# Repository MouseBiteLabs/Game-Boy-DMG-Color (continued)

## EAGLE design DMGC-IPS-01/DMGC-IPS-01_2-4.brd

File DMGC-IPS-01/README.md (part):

# DMGC-IPS-01

*The image above of the assembled board is of v2.0, not the current revision of v2.4. The differences are very minor, see below.*

The IPS board is in the front of the DMG shell. This holds the IPS screen kit (and has pads for interfacing with it), has the dimmable power LED, button inputs along with pads for optional LEDs, a navigation switch on the side for changing settings on the IPS screen and the backlit buttons, and the speaker.

For a technical explanation of the CPU board, please view the README in the Technical folder.

## Board Characteristics

The zipped folder contains all the gerber files for this board.
-	Layers: 2
-	Thickness: 1.2 mm
-	Surface Finish: ENIG or HASL (SEE NOTE!)

*ENIG is required for reliable button press detection; you can use HASL if you are using tactile switches.*

<a href="https://www.etsy.com/listing/1331663235/game-boy-dmgc-ips-board">**I sell this board on Etsy, so you don't have to buy multiples from board fabricators.**</a>

You can alternatively use the zipped folder at any board fabricator you like. You may also buy the board from PCBWay using this link (disclosure: I receive 10% of the  sale value to go towards future PCB orders):

## Customization Options

This section will explain all of the different customization options available on this board while assembling.

### Tactile Switches

Version 2.0 introduced the option for including tactile switches for the buttons, much like the Game Boy Advance SP had. If you do not wish to use these kinds of buttons, the button contacts are still set up to act just like the regular set up with membranes.

In this image, tactile switches are on the left, and pads for simple membranes are on the right. Either method for button presses works perfectly fine. But make sure you put them in the correct way. The little "wings" on the switches should be oriented where there is blank board space.

If you're doing tactile switches on the start and select buttons, you should do a trace cut as indicated where the white lines are pointing. If you don't, the membranes can still activate the start/select buttons on the exposed area without actuating the tactile switch. You may also want to tape over the exposed copper not underneath the switches while soldering them on to avoid getting stray solder on the exposed traces and ruin the A E S T H E T I C.

### Power LED Brightness

Increase the value of R1 to decrease the brightness of the power LED during normal battery levels. Increase the value of R2 to decrease the brightness of the power LED during low battery levels. It is suggested to try changing resistances in ~5 kΩ increments.

### Backlit Buttons

There are a few different avenues to take with respect to the button LEDs. You can use the RGB NeoPixels, discrete always-on LEDs, or none at all.

1) **No Button LEDs:** You do not need to populate LED10-LED17, R9, R22-R29, C2, or U2. Carry on.

2) **Always-on Single Color Backlit Buttons:** If you only want backlit buttons with non-controllable LEDs, you can omit R9, C2, and U2. 

You must isntead install R22-R29, as well as the discrete 0603 LEDs. An 0603 LED will fit on half of the 4-pin RGB LED pads, from VDD to DO. The pads for this are indicated by the arrows. The picture below shows which pads to use for discrete LEDs (view of the D-pad) - the A indicates the anode of the diode. There are spaces for a resistor for each LED on the back of the board (R22 to R29, circled in red below). If you're using the RGB LEDs, or no LEDs at all, the resistors aren't necessary. R22-R29 control the brightness of the LEDs, so keep in mind a higher resistance means lower brightness.

3) **RGB Backlit Buttons:** If you would like RGB LEDs behind the buttons, you must install LED10-LED17, R9, C2, and U2. Do not populate R22-R29.

When you solder the LEDs on, I recommend taping off the button contacts to make sure you don't get solder on them. It won't damage them to the point of non-function, but it can potentially reduce their useful lifetime and accurate detection depending on the severity. (But more importantly, it's not A E S T H E T I C)

If you install the LEDs and determine they just aren't for you, but don't want want to spend time removing the LEDs themsleves, then bridging the solder pad labeled "NEOPIXEL DISABLE" will ground the navigation switch push function, preventing the LEDs from turning on at all.

#### Programming the ATTINY85

An easy way to program the ATTINY with the code for the backlit buttons is to use an Arduino Uno or Arduino Mega. Check out these tutorials for how to program ATTINY chips with them:

-	<a href="https://www.instructables.com/How-to-Burn-ATTiny85-Using-Arduino-Mega/">Instructables post for programming an ATTINY85 with an Arduino Mega</a>
-	<a href="https://www.instructables.com/How-to-Program-an-Attiny85-From-an-Arduino-Uno/">Instructables post for programming an ATTINY85 with an Arduino Uno</a>

The code is provided above (the .ino file) and you will likely need to install Adafruit's NeoPixel library as well to get it to compile correctly. That can be found here:

- <a href="https://learn.adafruit.com/adafruit-neopixel-uberguide/arduino-library-installation">Installing Adafruit's NeoPixel Library to Arduino IDE</a>

If you're programming the ATTINY while it's installed on the IPS board, be sure to remove the cables from J1 and J2, otherwise your Arduino will attempt to backfeed the Gameboy and/or the IPS screen kit.

You can use the 7-pin connector on the side of the IPS board to connect to the ATTINY if it's already on the PCB. (You don't need the 3.3V pin to program, it's there for helping you develop your own ATTINY code if you want to use it)

**NOTE: VERSION DIFFERENCE**

On the v2.0 and v2.1 boards, pins 1 and 8 are flipped! And the 3.3V pin does not exist.

### Adding Reset Button Functionality

- If you are using the push function of the navigation switch to reset the console instead of controlling the button LEDs (see more info on the CPU README), then **make sure to remove R10.** You will not have the ability to control Neopixel LEDs with this change (without other code/hardware modifications).
- If you are using the rock down function of the navigation switch to reset the console instead of controlling the Q5 palette setting (see more info on the CPU README), then **make sure to remove C5.** You will not have the ability to use the palette swap function of the Q5 kit with this change (but who really cares, amirite?)

### Alternate OSD Controls

You don't need to use the SEL, A, and B pads at the top of the board for the OSD controls. You can alternatively use the button pads in the middle of the board instead. For example, if you intend to use LSDJ on the DMGC, you might run into a conflict with pressing A + B + Select. This is a specific combination for control in LSDJ. So instead for OSD control, you can run wires down to the middle of the board. Instead of A, B, and Select, you could pick A, B, and Start for example. Just keep in mind you have to press all three at the same time to open the menu, so don't pick Left and Right as two of the inputs, for example.

## Bill of Materials

Here, I have provided links to components I used personally (or suitable replacements). This BOM is also included in Excel format in the root folder.

| Reference Designators   | Qty | Value/Part Number | Package             | Description                       | Comment                                                                                                                            | Source                                                                                                                                                                                                                               |
| ----------------------- | --- | ----------------- | ------------------- | --------------------------------- | ---------------------------------------------------------------------------------------------------------------------------------- | ------------------------------------------------------------------------------------------------------------------------------------------------------------------------------------------------------------------------------------ |
| B1-B8                   | 8   | SKRRABE010        |                     | Tactile switch                    | Optional, can be omitted if you don't want clicky SP-style buttons (SKRRAA is less clicky, SKRRAC is more clicky)                  | [https://www.mouser.com/ProductDetail/688-SKRRAB](https://www.mouser.com/ProductDetail/688-SKRRAB)                                                                                                                                   |
| C1, C2, C6, C7, C8, C24 | 6   | 0.1uF             | 0603                | Capacitor (MLCC)                  | Should be X5R (or better), at least 16V                                                                                            | [https://www.mouser.com/ProductDetail/?qs=l5k%252BbMnNDknCtKnMv1oEgA%3D%3D](https://www.mouser.com/ProductDetail/?qs=l5k%252BbMnNDknCtKnMv1oEgA%3D%3D)                                                                               |
| C3                      | 1   | 100uF             |                     | Capacitor (Aluminum electrolytic) | Board has space for a 100uF SMD tantalum electrolytic instead                                                                      | [https://www.mouser.com/ProductDetail/KEMET/ESK107M010AC3AA?qs=9RUIYXQlAdBiO30krUyznA%3D%3D](https://www.mouser.com/ProductDetail/KEMET/ESK107M010AC3AA?qs=9RUIYXQlAdBiO30krUyznA%3D%3D)                                             |
| C4, C5                  | 2   | 100pF             | 0603                | Capacitor (MLCC)                  |                                                                                                                                    | [https://www.mouser.com/ProductDetail/YAGEO/CC0603JPNPO9BN101?qs=7s%252B3O6pAiyAo%2FUxNqKltRA%3D%3D](https://www.mouser.com/ProductDetail/YAGEO/CC0603JPNPO9BN101?qs=7s%252B3O6pAiyAo%2FUxNqKltRA%3D%3D)                             |
| C9, C10                 | 2   | 27pF              | 0603                | Capacitor (MLCC)                  |                                                                                                                                    | [https://www.mouser.com/ProductDetail/603-C0603FRNPO9BN270](https://www.mouser.com/ProductDetail/603-C0603FRNPO9BN270)                                                                                                               |
| FFC Cable               | 1   | 15020-0541        |                     | Flat Flexible Cable               | Gold plated preferred, but alternate part can work too. Note that 15020-0541 must be bent in the proper direction for good fitment | [https://www.mouser.com/ProductDetail/Molex/15020-0541?qs=pwzmk436yFR5fXbQvbR%2F1w%3D%3D](https://www.mouser.com/ProductDetail/Molex/15020-0541?qs=pwzmk436yFR5fXbQvbR%2F1w%3D%3D)                                                   |
| J1, J2                  | 2   | 62684-502100AHLF  |                     | FFC connector                     |                                                                                                                                    | https://www.mouser.com/ProductDetail/?qs=HL%252BYNjdyZ0vzwc9E0QYY2g%3D%3D                                                                                                                                                            |
| J3                      | 1   | TSM-107-01-T-SH   |                     | Surface Mount Terminal Strip      | Optional for assembly, only helpful for programming the ATTINY                                                                     | [https://www.mouser.com/ProductDetail/200-TSM10701TSH](https://www.mouser.com/ProductDetail/200-TSM10601TSH)                                                                                                                         |
| LED1                    | 1   | 151033RS03000     | 3mm                 | Red LED                           |                                                                                                                                    | [https://www.mouser.com/ProductDetail/Wurth-Elektronik/151033RS03000?qs=LlUlMxKIyB1%252BAw6bWFN43w%3D%3D](https://www.mouser.com/ProductDetail/Wurth-Elektronik/151033RS03000?qs=LlUlMxKIyB1%252BAw6bWFN43w%3D%3D)                   |
| LED10-LED17             | 8   | WS2812            | 2020                | RGB LED                           | Link leads to a 10-pack. Discrete 0603-size LEDs can be used instead                                                               | [https://www.mouser.com/ProductDetail/Adafruit/4684?qs=DPoM0jnrROWIv9%2FMCIm5vw%3D%3D](https://www.mouser.com/ProductDetail/Adafruit/4684?qs=DPoM0jnrROWIv9%2FMCIm5vw%3D%3D)                                                         |
| Q1                      | 1   | 2N7002            | SOT23               | N-channel MOSFET                  |                                                                                                                                    | [https://www.mouser.com/ProductDetail/Nexperia/2N7002NXBKR?qs=%252B6g0mu59x7J2ddJstTJGkQ%3D%3D](https://www.mouser.com/ProductDetail/Nexperia/2N7002NXBKR?qs=%252B6g0mu59x7J2ddJstTJGkQ%3D%3D)                                       |
| R1, R14                 | 2   | 10k               | 0603                | Resistor                          |                                                                                                                                    | [https://www.mouser.com/ProductDetail/YAGEO/RC0603FR-0710KL?qs=grNVn54RoB%252B3GtjbJj3wJQ%3D%3D](https://www.mouser.com/ProductDetail/YAGEO/RC0603FR-0710KL?qs=grNVn54RoB%252B3GtjbJj3wJQ%3D%3D)                                     |
| R22-R29                 | 8   | 10k               | 0603                | Resistor                          | Only if using discrete LEDs for LED10-LED17 (adjust resistance for brightness)                                                     | [https://www.mouser.com/ProductDetail/YAGEO/RC0603FR-0710KL?qs=grNVn54RoB%252B3GtjbJj3wJQ%3D%3D](https://www.mouser.com/ProductDetail/YAGEO/RC0603FR-0710KL?qs=grNVn54RoB%252B3GtjbJj3wJQ%3D%3D)                                     |
| R2, R6, R7              | 3   | 18k               | 0603                | Resistor                          |                                                                                                                                    | [https://www.mouser.com/ProductDetail/YAGEO/RC0603FR-1018KL?qs=qpJ%252B%252B%252Bdg6p1T2VMMxU7GeA%3D%3D](https://www.mouser.com/ProductDetail/YAGEO/RC0603FR-1018KL?qs=qpJ%252B%252B%252Bdg6p1T2VMMxU7GeA%3D%3D)                     |
| R3, R5, R11, R12        | 4   | 402k              | 0603                | Resistor                          |                                                                                                                                    | [https://www.mouser.com/ProductDetail/YAGEO/RC0603FR-07402KL?qs=e5TEs1AaK9ZgNZ9JLlILuQ%3D%3D](https://www.mouser.com/ProductDetail/YAGEO/RC0603FR-07402KL?qs=e5TEs1AaK9ZgNZ9JLlILuQ%3D%3D)                                           |
| R4                      | 1   | 100               | 0603                | Resistor                          |                                                                                                                                    | [https://www.mouser.com/ProductDetail/YAGEO/RC0603FR-07100RL?qs=NEN%2FsE%2FLsvPIwIWKCOS4%2FA%3D%3D](https://www.mouser.com/ProductDetail/YAGEO/RC0603FR-07100RL?qs=NEN%2FsE%2FLsvPIwIWKCOS4%2FA%3D%3D)                               |
| R8, R10                 | 2   | 100k              | 0603                | Resistor                          |                                                                                                                                    | [https://www.mouser.com/ProductDetail/YAGEO/RC0603FR-07100KL?qs=e1ok2LiJcmaihem8Va5%2Fsw%3D%3D](https://www.mouser.com/ProductDetail/YAGEO/RC0603FR-07100KL?qs=e1ok2LiJcmaihem8Va5%2Fsw%3D%3D)                                       |
| R9                      | 1   | 510               | 0603                | Resistor                          |                                                                                                                                    | [https://www.mouser.com/ProductDetail/YAGEO/RC0603FR-07510RL?qs=gt6vzsuosg04lV7mPQHzdw%3D%3D](https://www.mouser.com/ProductDetail/YAGEO/RC0603FR-07510RL?qs=gt6vzsuosg04lV7mPQHzdw%3D%3D)                                           |
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
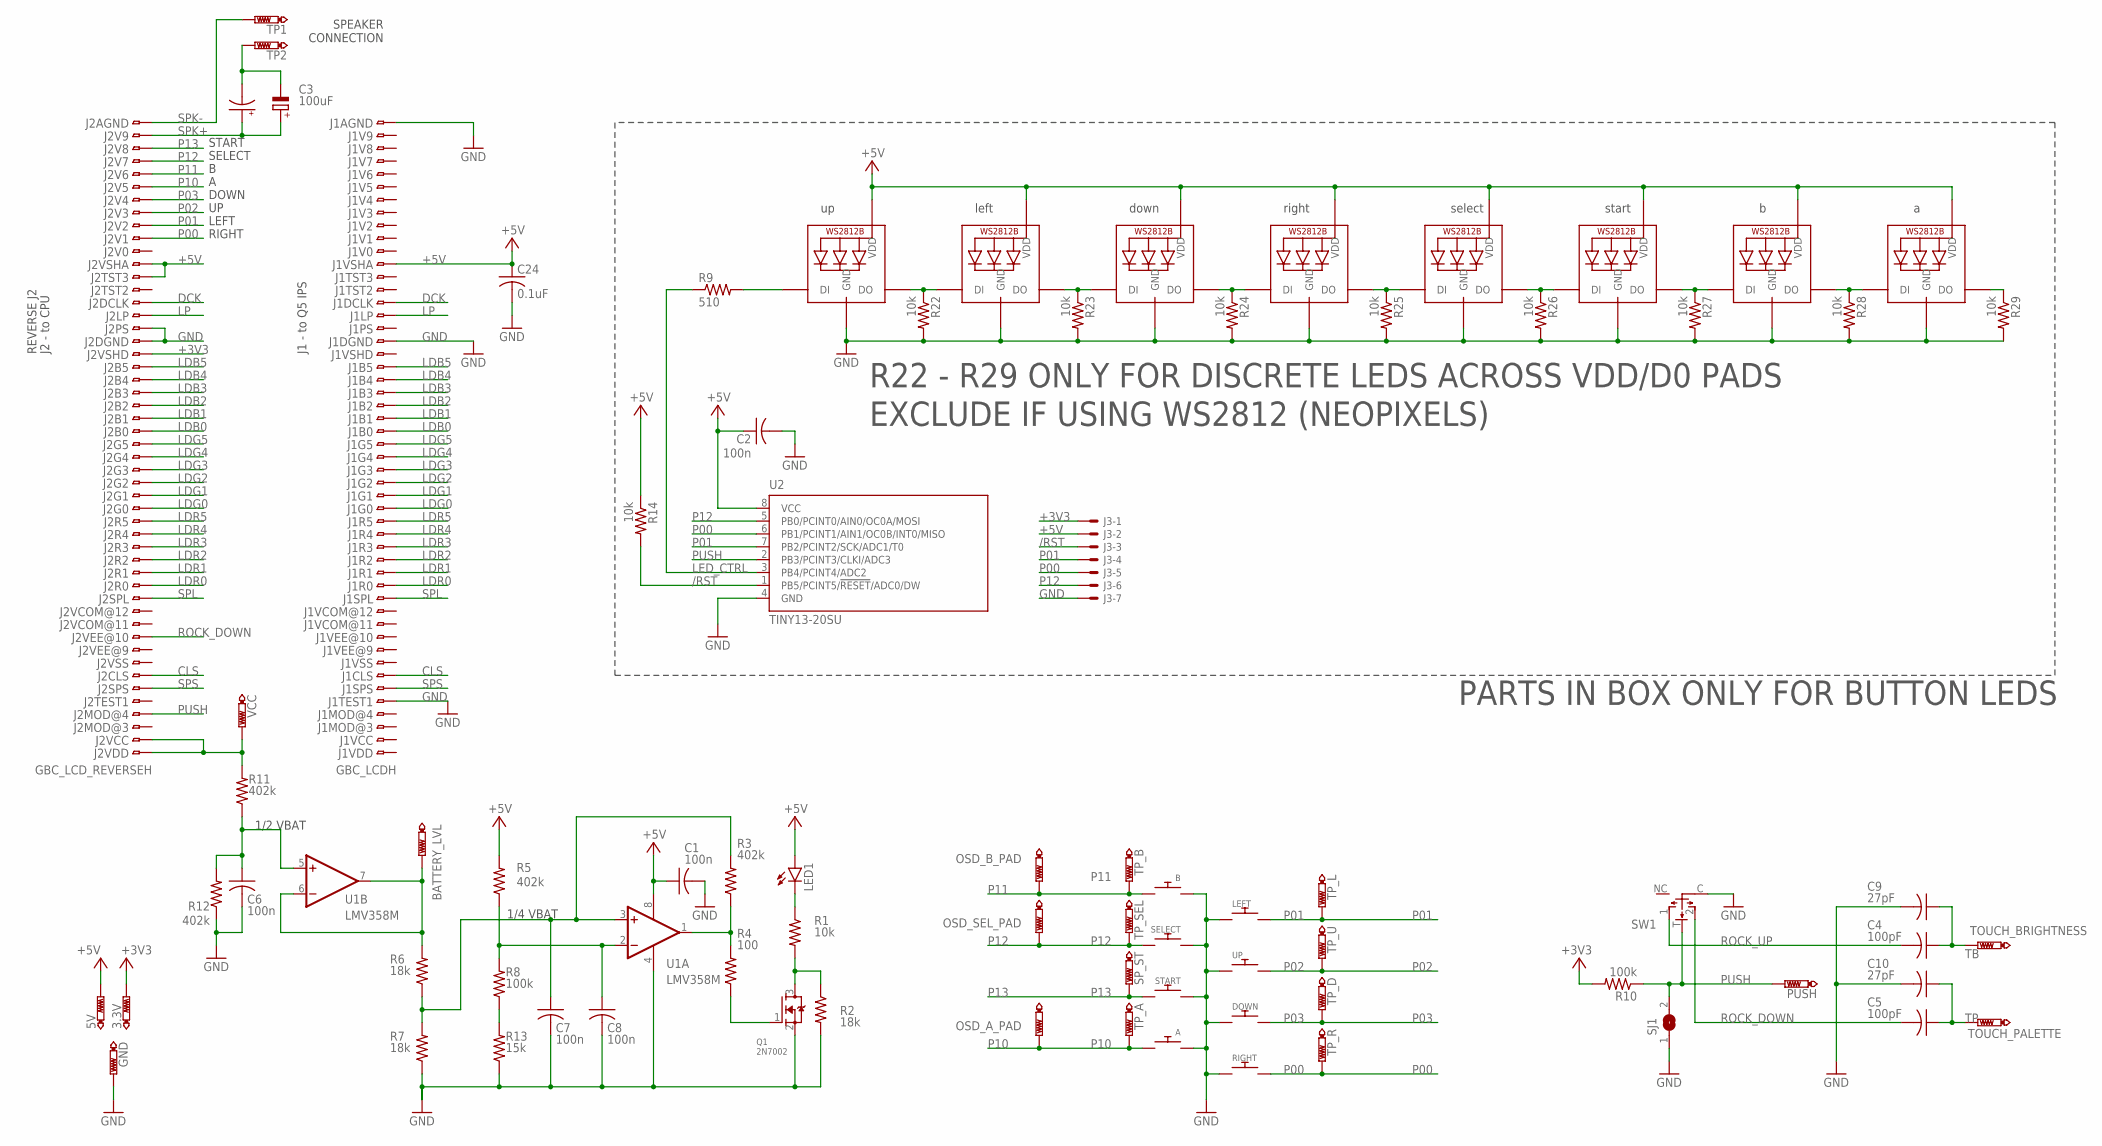
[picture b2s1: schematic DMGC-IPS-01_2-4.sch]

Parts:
3.3V, 5V: PTR1TP20R; TP20R
A: DMG-BTN; DMG_BTN1
B: DMG-BTN; DMG_BTN1
BATTERY_LVL: PTR1TP20R; TP20R
C1, C2, C6, C7, C8: 100n; C0603
C3: 100uF; CT3528
C3TH: CPOL-EUE2,5-6E; E2,5-6E
C4, C5: 100pF; C0603
C9, C10: 27pF; C0603
C24: 0.1uF; C0603
DOWN: DMG-BTN; DMG_BTN1
GND: PTR1TP20R; TP20R
J1: GBC_LCDH; 62684-502100AHLF
J2: GBC_LCD_REVERSEH; 62684-502100AHLF_REVERSE
J3: C-GRID-07-15-91; 15-91-07
LED1: LED3MM
LED10, LED11, LED12, LED13, LED14, LED15, LED16, LED17: WS2812B3535; LED3535
LEFT: DMG-BTN; DMG_BTN1
OSD_A_PAD: PTR1TP20R; TP20R
OSD_B_PAD: PTR1TP20R; TP20R
OSD_SEL_PAD: PTR1TP20R; TP20R
PUSH: PTR1TP20R; TP20R
Q1: 2N7002; SOT23
R1, R14, R22, R23, R24, R25, R26, R27, R28, R29: 10k; R0603
R2, R6, R7: 18k; R0603
R3, R5, R11, R12: 402k; R0603
R4: 100; R0603
R8, R10: 100k; R0603
R9: 510; R0603
R13: 15k; R0603
RIGHT: DMG-BTN; DMG_BTN1
SELECT: DMG-BTN; DMG_BTN2_TACT2
SJ1: SJ
SP_ST: PTR1TP20R; TP20R
START: DMG-BTN; DMG_BTN2_TACT2
SW1: NAV_SWITCH
TOUCH_BRIGHTNESS: PTR1TP20R; TP20R
TOUCH_PALETTE: PTR1TP20R; TP20R
TP1, TP2: PTR1PAD1-13; P1-13
TP_A: PTR1TP20R; TP20R
TP_B: PTR1TP20R; TP20R
TP_D: PTR1TP20R; TP20R
TP_L: PTR1TP20R; TP20R
TP_R: PTR1TP20R; TP20R
TP_SEL: PTR1TP20R; TP20R
TP_U: PTR1TP20R; TP20R
U1: LMV358M; SO08
U2: TINY13-20SU; 8S2
UP: DMG-BTN; DMG_BTN1
VCC: PTR1TP20R; TP20R

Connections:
+3V3: 3.3V.TP, J2.19, J3.1, R10.2
+5V: 5V.TP, C1.1, C2.1, C24.1, J1.39, J2.12, J2.13, J3.2, LED1.A, LED10.4 (VDD), LED11.4 (VDD), LED12.4 (VDD), LED13.4 (VDD), LED14.4 (VDD), LED15.4 (VDD), LED16.4 (VDD), LED17.4 (VDD), R5.2, R14.1, U1.8 (V+), U2.8 (VCC)
/RST: J3.3, R14.2, U2.1 (PB5/PCINT5/!RESET!/ADC0/DW)
BATT: J2.49, J2.50, R11.2, VCC.TP
CLS: J1.7, J2.44
DCK: J1.36, J2.15
GND: A.P$2, B.P$2, C1.2, C2.2, C6.2, C7.2, C8.2, C9.2, C10.2, C24.2, DOWN.P$2, GND.TP, J1.5, J1.33, J1.50, J2.17, J2.18, J3.7, LED10.2 (GND), LED11.2 (GND), LED12.2 (GND), LED13.2 (GND), LED14.2 (GND), LED15.2 (GND), LED16.2 (GND), LED17.2 (GND), LEFT.P$2, Q1.2 (S), R2.2, R7.1, R12.1, R13.1, R22.2, R23.2, R24.2, R25.2, R26.2, R27.2, R28.2, R29.2, RIGHT.P$2, SELECT.P$1, SJ1.1, START.P$1, SW1.C, U1.4 (V-), U2.4 (GND), UP.P$2
LDB0: J1.26, J2.25
LDB1: J1.27, J2.24
LDB2: J1.28, J2.23
LDB3: J1.29, J2.22
LDB4: J1.30, J2.21
LDB5: J1.31, J2.20
LDG0: J1.20, J2.31
LDG1: J1.21, J2.30
LDG2: J1.22, J2.29
LDG3: J1.23, J2.28
LDG4: J1.24, J2.27
LDG5: J1.25, J2.26
LDR0: J1.14, J2.37
LDR1: J1.15, J2.36
LDR2: J1.16, J2.35
LDR3: J1.17, J2.34
LDR4: J1.18, J2.33
LDR5: J1.19, J2.32
LED_CTRL: R9.1, U2.3 (PB4/PCINT4/ADC2)
LP: J1.35, J2.16
unnamed: Q1.3 (D), R1.2, R2.1
unnamed: LED1.K (C), R1.1
unnamed: BATTERY_LVL.TP, R6.2, U1.6 (-IN), U1.7 (OUT)
unnamed: LED13.1 (DO), LED16.3 (DI), R27.1
unnamed: LED15.3 (DI), LED16.1 (DO), R28.1
unnamed: LED10.1 (DO), LED14.3 (DI), R22.1
unnamed: C8.1, R5.1, R8.2, U1.2 (-IN)
unnamed: LED11.3 (DI), LED14.1 (DO), R23.1
unnamed: LED11.1 (DO), LED12.3 (DI), R24.1
unnamed: LED12.1 (DO), LED17.3 (DI), R25.1
unnamed: LED13.3 (DI), LED17.1 (DO), R26.1
unnamed: LED15.1 (DO), R29.1
unnamed: LED10.3 (DI), R9.2
unnamed: C6.1, R11.1, R12.2, U1.5 (+IN)
unnamed: C3.-, C3TH.-, TP2.TP
unnamed: R8.1, R13.2
unnamed: C7.1, R3.2, R6.1, R7.2, U1.3 (+IN)
unnamed: R3.1, R4.2, U1.1 (OUT)
P00: J2.10, J3.5, RIGHT.P$1, TP_R.TP, U2.6 (PB1/PCINT1/AIN1/OC0B/INT0/MISO)
P01: J2.9, J3.4, LEFT.P$1, TP_L.TP, U2.7 (PB2/PCINT2/SCK/ADC1/T0)
P02: J2.8, TP_U.TP, UP.P$1
P03: DOWN.P$1, J2.7, TP_D.TP
P10: A.P$1, J2.6, OSD_A_PAD.TP, TP_A.TP
P11: B.P$1, J2.5, OSD_B_PAD.TP, TP_B.TP
P12: J2.4, J3.6, OSD_SEL_PAD.TP, SELECT.P$2, TP_SEL.TP, U2.5 (PB0/PCINT0/AIN0/OC0A/MOSI)
P13: J2.3, SP_ST.TP, START.P$2
PSU_EN: Q1.1 (G), R4.1
PUSH: J2.47, PUSH.TP, R10.1, SJ1.2, SW1.T, U2.2 (PB3/PCINT3/CLKI/ADC3)
ROCK_DOWN: C5.2, J2.41, SW1.2
ROCK_UP: C4.2, SW1.1
SPK+: C3.+, C3TH.+, J2.2
SPK-: J2.1, TP1.TP
SPL: J1.13, J2.38
SPS: J1.6, J2.45
TB: C4.1, C9.1, TOUCH_BRIGHTNESS.TP
TP: C5.1, C10.1, TOUCH_PALETTE.TP

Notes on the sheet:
REVERSE J2
J1 - to Q5 IPS
J2 - to CPU
1/2 VBAT
left
down
right
select
start
1/4 VBAT
R22 - R29 ONLY FOR DISCRETE LEDS ACROSS VDD/D0 PADS
START SELECT B A DOWN UP LEFT RIGHT
SPEAKER CONNECTION
EXCLUDE IF USING WS2812 (NEOPIXELS)
PARTS IN BOX ONLY FOR BUTTON LEDS

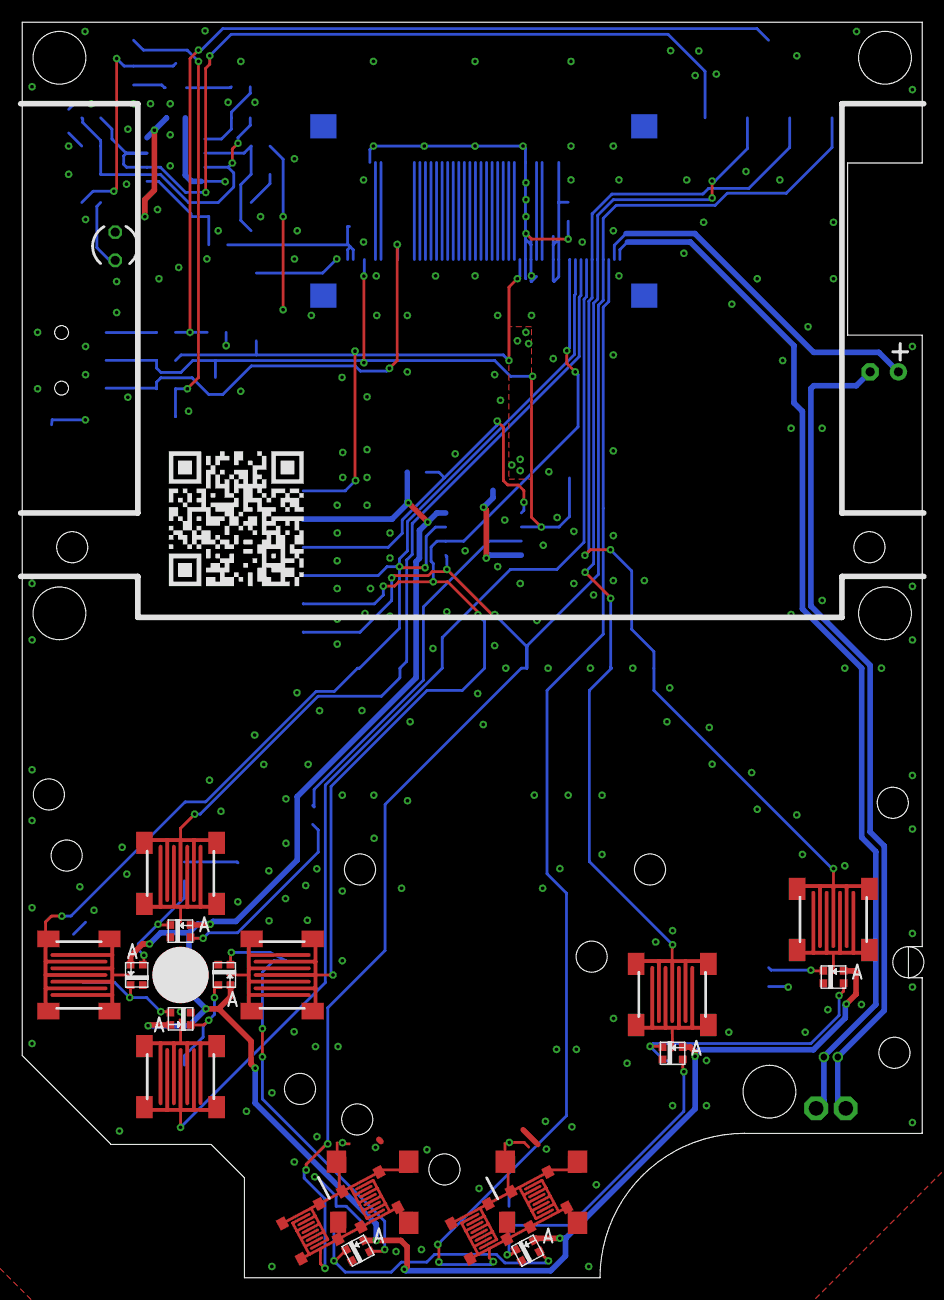
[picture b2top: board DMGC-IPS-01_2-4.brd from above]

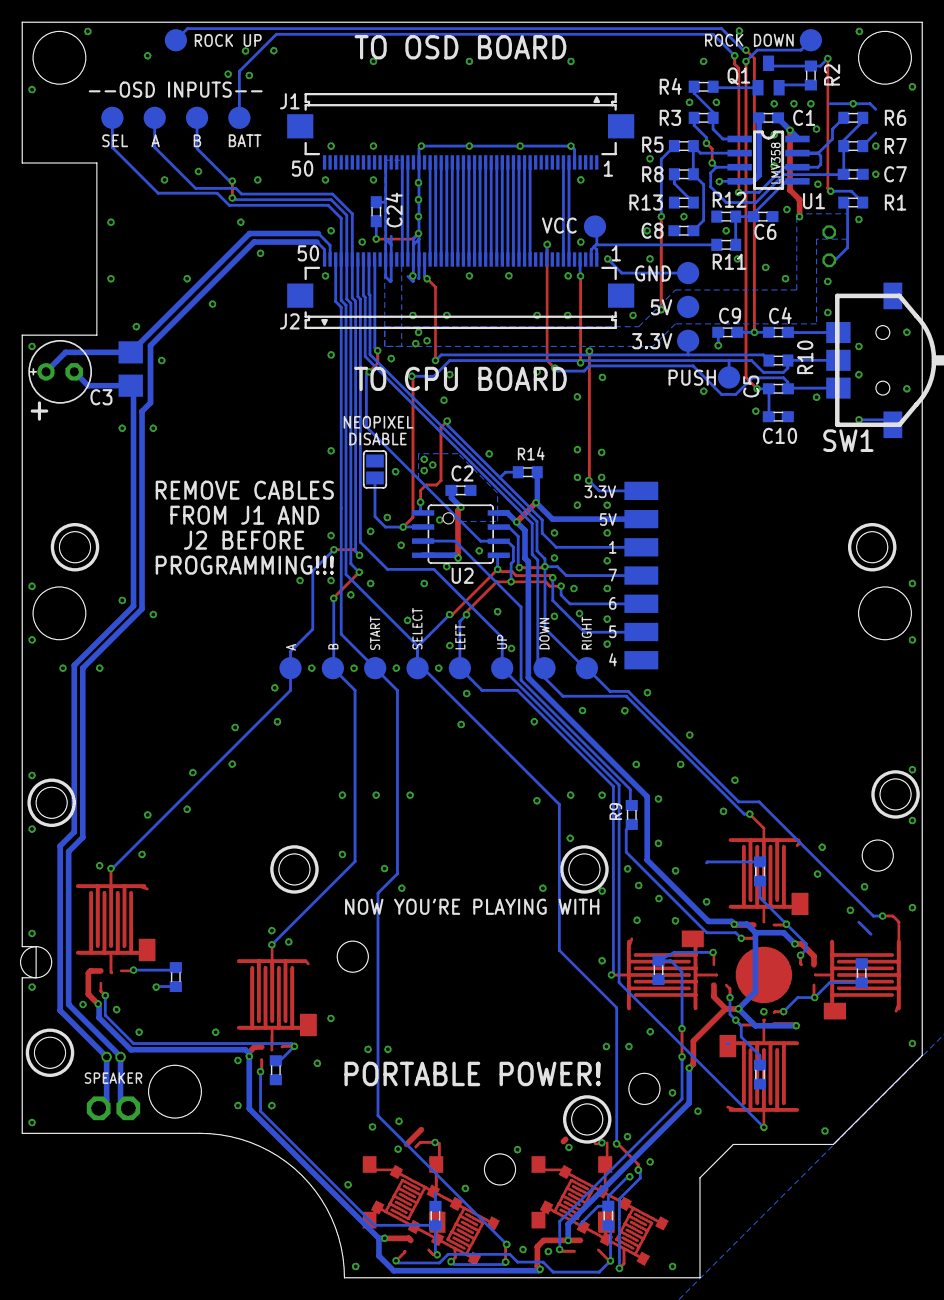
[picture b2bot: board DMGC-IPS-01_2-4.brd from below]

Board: 2 copper layers, 81.0 x 113.0 mm, 80 parts (61 on the bottom side), 63 nets.

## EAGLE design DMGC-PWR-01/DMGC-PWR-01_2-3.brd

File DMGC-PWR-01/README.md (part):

# DMGC-PWR-01

*Note: This image shows v2.0. There is minimal difference between this and v2.3.*

The PWR board has gone through a few iterations. Because the system will run with 4x AA batteries or the DC jack input, the range of input voltages is relatively wide - anywhere between ~4 V up to ~8 V, plus margin. The output voltage must be maintained at 5 V. The logical choice would be a buck-boost converter. Thus, the DMGC-PWR-01 utilizes the TPS630702 (or TPS63070 or TPS630701) – a buck-boost converter with only a few external parts required for operation, that accepts anywhere between 2 V and 16 V to produce a 5 V output.

This board is likely the most complex part of the build. I spent a lot of time tuning the circuit to produce the exact results I wanted with ample protection downstream of the converters.

For a technical explanation of the CPU board, please view the README in the Technical folder.

## Board Characteristics
The zipped folder contains all the gerber files for this board.
-	Layers: 2
-	Thickness: 1.2 mm or smaller
-	Surface Finish: ENIG or HASL

*HASL is acceptable, but might introduce a bit of difficulty soldering the QFN chip owing to the possibly uneven surface compared to an ENIG finish.*

<a href="https://www.etsy.com/listing/1317694018/game-boy-dmgc-pwr-board">**I sell this board on Etsy, so you don't have to buy multiples from board fabricators.**</a>

You can alternatively use the zipped folder at any board fabricator you like. You may also buy the board from PCBWay using this link (disclosure: I receive 10% of the sale value to go towards future PCB orders):

## Configuring for Different TPS chips on U2

For TPS63070 or TPS630702, R8 needs to be 523k and R9 needs to be 100k, as indicated in the BOM.

For TPS630701, you need to short R8 with a solder bridge/wire or a zero ohm resistor, and remove R9 completely.

**It is critical you configure the board correctly, otherwise you may damage your system.**

## Using in an Original DMG (UNTESTED!)

This board can (probably) be used as a replacement to the original DMG power board, provided you are using an IPS screen that only requires a 5 V output. This board will not supply voltages for the LCD, so it cannot be used in an unmodded DMG.

Follow the silkscreen on the back of the board to connect wires to the DMG motherboard, as shown below (image from Gekkio's Game Boy Hardware Database: https://gbhwdb.gekkio.fi/consoles/dmg/). The red wire on the main DMG CPU board indicates pin 1. The blue box on the back of the DMG CPU board indicates the connection for the BAT hole.

IF you happen to test this (at your own risk!) let me know your results.

## Bill of Materials

Here, I have provided links to components I used personally (or suitable replacements). This BOM is also included in Excel format in the root folder.

| Reference Designators         | Qty | Value/Part Number              | Package    | Description          | Comment                                                                                                                               | Source                                                                                                                                                                                                                                                                                   |
| ----------------------------- | --- | ------------------------------ | ---------- | -------------------- | ------------------------------------------------------------------------------------------------------------------------------------- | ---------------------------------------------------------------------------------------------------------------------------------------------------------------------------------------------------------------------------------------------------------------------------------------- |
| C1, C5, C6                    | 3   | 10uF                           | 0603       | Capacitor (MLCC)     | Should be X5R (or better), at least 16V                                                                                               | [https://www.mouser.com/ProductDetail/Murata-Electronics/GRM188R61E106KA73J?qs=5aG0NVq1C4xEV8YyiSS7mg%3D%3D&countrycode=US&currencycode=USD](https://www.mouser.com/ProductDetail/Murata-Electronics/GRM188R61E106KA73J?qs=5aG0NVq1C4xEV8YyiSS7mg%3D%3D&countrycode=US&currencycode=USD) |
| C3, C4                        | 2   | 22uF                           | 1206       | Capacitor (MLCC)     | Should be X5R (or better), at least 16V                                                                                               | [https://www.mouser.com/ProductDetail/Samsung-Electro-Mechanics/CL31A226KAHNNNE?qs=X6jEic%2FHinCdwsjGJII51w%3D%3D](https://www.mouser.com/ProductDetail/Samsung-Electro-Mechanics/CL31A226KAHNNNE?qs=X6jEic%2FHinCdwsjGJII51w%3D%3D)                                                     |
| C7                            | 1   | 47uF                           | 1206       | Capacitor (MLCC)     | Should be X5R (or better), at least 16V                                                                                               | [https://www.mouser.com/ProductDetail/Murata-Electronics/GRM31CR61C476ME44K?qs=QzBtWTOodeVeYV6UhCOqow%3D%3D](https://www.mouser.com/ProductDetail/Murata-Electronics/GRM31CR61C476ME44K?qs=QzBtWTOodeVeYV6UhCOqow%3D%3D)                                                                 |
| C8, C9, C11                   | 3   | 0.1uF                          | 0603       | Capacitor (MLCC)     |                                                                                                                                       | [https://www.mouser.com/ProductDetail/?qs=l5k%252BbMnNDknCtKnMv1oEgA%3D%3D](https://www.mouser.com/ProductDetail/?qs=l5k%252BbMnNDknCtKnMv1oEgA%3D%3D)                                                                                                                                   |
| C10                           | 1   | 0.01uF                         | 0603       | Capacitor (MLCC)     |                                                                                                                                       | [https://www.mouser.com/ProductDetail/KEMET/C0603C103J5RACTU?qs=BimOss5pjlFJEfKhlb7g1g%3D%3D](https://www.mouser.com/ProductDetail/KEMET/C0603C103J5RACTU?qs=BimOss5pjlFJEfKhlb7g1g%3D%3D)                                                                                               |
| F1                            | 1   | 1A                             | 0603       | Fuse                 |                                                                                                                                       | [https://www.mouser.com/ProductDetail/Vishay-Beyschlag/MFU0603FF01000P100?qs=oI046glRurtlP8n%252B3l7CPg%3D%3D](https://www.mouser.com/ProductDetail/Vishay-Beyschlag/MFU0603FF01000P100?qs=oI046glRurtlP8n%252B3l7CPg%3D%3D)                                                             |
| L1                            | 1   | 1.5uH                          | 1212       | Inductor             | Saturation current should be at least 2A                                                                                              | [https://www.mouser.com/ProductDetail/70-IHLP1212BZER1R5M1](https://www.mouser.com/ProductDetail/70-IHLP1212BZER1R5M1)                                                                                                                                                                   |
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
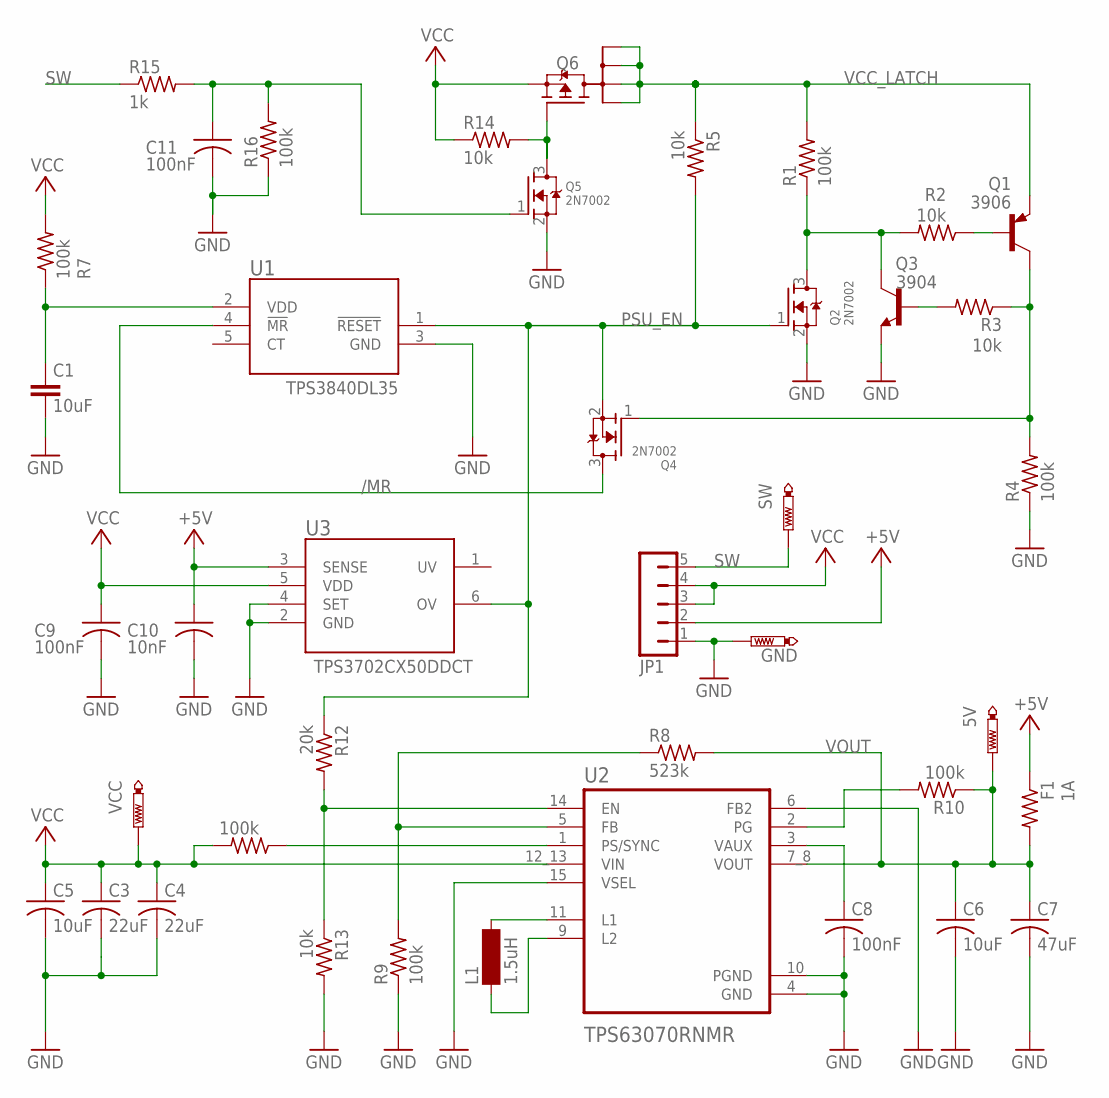
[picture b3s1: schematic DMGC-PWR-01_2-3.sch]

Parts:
5V: PTR1B1,27; B1,27
C1, C5, C6: 10uF; C0603
C3, C4: 22uF; C1206
C7: 47uF; C1206
C8, C9, C11: 100nF; C0603
C10: 10nF; C0603
F1: 1A; R0603
GND: PTR1B1,27; B1,27
JP1: JP5
L1: 1.5uH; 1212
Q1: MMBT3906LT1SMD; SOT23-BEC
Q2, Q4, Q5: 2N7002; SOT23
Q3: 3904; SOT23-BEC
Q6: SI1401EDH; SOT363_INFINEON
R1, R4, R7, R9, R10, R11, R16: 100k; R0603
R2, R3, R5, R13, R14: 10k; R0603
R8: 523k; R0603
R12: 20k; R0603
R15: 1k; R0603
SW: PTR1B1,27; B1,27
U1: TPS3840; SOT-23-5
U2: TPS63070RNMR; VREG_TPS63070RNMR
U3: TPS3702; SOT-23-6
VCC: PTR1B1,27; B1,27

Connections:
+5V: C10.1, F1.1, JP1.2, U3.3 (SENSE)
/MR: Q4.3 (D), U1.4 (!MR)
EN: R12.2, R13.1, U2.14 (EN)
GND: C1.2, C3.2, C4.2, C5.2, C6.2, C7.2, C8.2, C9.2, C10.2, C11.2, GND.TP, JP1.1, Q2.2 (S), Q3.E, Q5.2 (S), R4.1, R9.1, R13.2, R16.1, U1.3 (GND), U2.4 (GND), U2.6 (FB2), U2.10 (PGND), U2.15 (VSEL), U3.2 (GND), U3.4 (SET)
unnamed: C1.1, R7.1, U1.2 (VDD)
unnamed: L1.2, U2.11 (L1)
unnamed: L1.1, U2.9 (L2)
unnamed: R10.2, U2.2 (PG)
unnamed: C8.1, U2.3 (VAUX)
unnamed: R8.1, R9.2, U2.5 (FB)
unnamed: Q5.3 (D), Q6.3 (G), R14.2
unnamed: C11.1, Q5.1 (G), R15.2, R16.2
unnamed: Q1.B, R2.1
unnamed: Q1.C, Q4.1 (G), R3.1, R4.2
unnamed: Q3.B, R3.2
unnamed: Q2.3 (D), Q3.C, R1.1, R2.2
PS: R11.1, U2.1 (PS/SYNC)
PSU_EN: Q2.1 (G), Q4.2 (S), R5.2, R12.1, U1.1 (!RESET), U3.6 (OV)
SW: JP1.5, R15.1, SW.TP
VCC: C3.1, C4.1, C5.1, C9.1, JP1.3, JP1.4, Q6.4 (S), R7.2, R11.2, R14.1, U2.12_13 (VIN), U3.5 (VDD), VCC.TP
VCC_LATCH: Q1.E, Q6.1 (D1), Q6.2 (D2), Q6.5 (D5), Q6.6 (D6), R1.2, R5.1
VOUT: 5V.TP, C6.1, C7.1, F1.2, R8.2, R10.1, U2.7_8 (VOUT)

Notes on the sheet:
3906
TPS3840DL35
TPS3702CX50DDCT

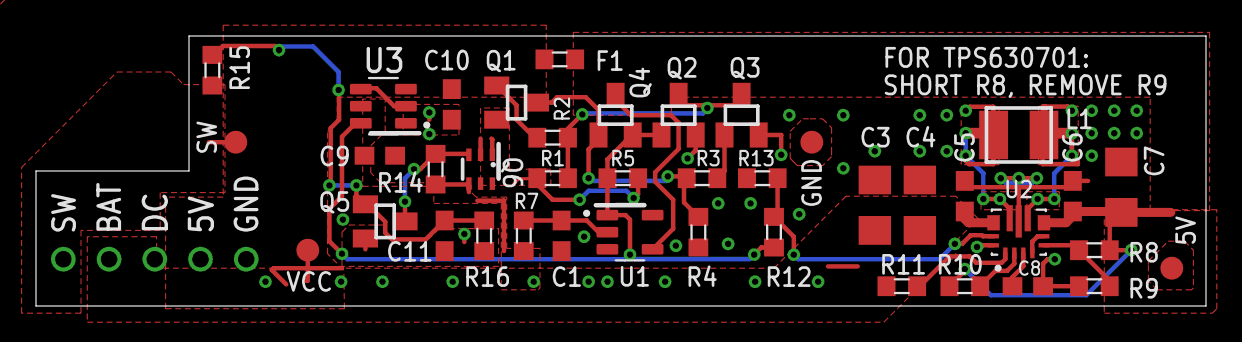
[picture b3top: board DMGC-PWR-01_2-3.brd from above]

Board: 2 copper layers, 65.0 x 15.0 mm, 41 parts (0 on the bottom side), 22 nets.

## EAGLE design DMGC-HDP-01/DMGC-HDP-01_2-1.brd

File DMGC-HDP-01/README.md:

# DMGC-HDP-01

*The image above is of v2.0, not the current revision of v2.1. The differences are very minor, see below.*

This little board is quite simple. You can transplant all of the parts from the original DMG headphone board to this one. This board also uses an original DMG headphone jack. Modifications to the circuit would be required to use an off-the-shelf jack.

## Board Characteristics
The zipped folder contains all the gerber files for this board.
-	Layers: 2
-	Thickness: 1.2 mm or 1.6 mm
-	Surface Finish: HASL
- **NOTE: When ordering PCBs, add this note to the order: "The file milling.gbr contains outlines for plated slots. Please add plated slots on the PCB according to this layer."**

<a href="https://www.etsy.com/listing/1331671237/game-boy-dmgc-hdp-board-headphone-board">**I sell this board on Etsy, so you don't have to buy multiples from board fabricators.**</a>

You can alternatively use the zipped folder at any board fabricator you like. You may also buy the board from PCBWay using this link (disclosure: I receive 10% of the  sale value to go towards future PCB orders):

## Circuit Overview

On the top of the board: pin 1 is the left output, pin 2 is the right output, pin 3 is the GND reference, and pin 4 is the headphone detect pin which is normally connected to GND through the headphone jack (when headphones are placed in the jack, pin 4 will be disconnected from GND).

R1 and R2 are included to pull down the negative sides of the DC blocking capacitors C1 and C2 when headphones are not connected – without them, the outputs would be floating. This will prevent inrush current during headphone insertion, which I have seen cause issues with the LM4853 in the past.

On v2.1, C1 and C2 can be replaced with tantalum electrolytic capacitors if you would like - the pads are for size 1411 (3528 metric).

## Using the Original DMG Headphone Board

You can easily use the original DMG board instead of ordering this one, just be sure to put 1 kΩ resistors from the right output and left output to ground. Otherwise, when plugging in headphones, the system might shut itself off.

## Bill of Materials

All of the parts from the original headphone board can be transplanted here (except the two 1k resistors). You can even use the original headphone board if you want, just add the 1k resistors as indicated on the schematic. This BOM is also included in Excel format in the root folder.

| Reference Designators | Qty | Value/Part Number | Package | Description                       | Comment                                                                                                                           | Source                                                                                                                                                                                       |
| --------------------- | --- | ----------------- | ------- | --------------------------------- | --------------------------------------------------------------------------------------------------------------------------------- | -------------------------------------------------------------------------------------------------------------------------------------------------------------------------------------------- |
| C1, C2                | 2   | 100uF             |         | Capacitor (Aluminum electrolytic) | Can be salvaged from DMG instead                                                                                                  | [https://www.mouser.com/ProductDetail/Panasonic/ECE-A0JKA101I?qs=WYPlz5ezODCWQbvWRFj8Mg%3D%3D](https://www.mouser.com/ProductDetail/Panasonic/ECE-A0JKA101I?qs=WYPlz5ezODCWQbvWRFj8Mg%3D%3D) |
| L1, L2, L3            | 3   | 3.3uH             |         | Filter                            | Surface mount replacement: https://www.mouser.com/ProductDetail/Murata-Electronics/BLM18BD102SN1D?qs=h3IWXJJGQQWi4eZyJq6ScQ%3D%3D | Salvaged (DMG)                                                                                                                                                                               |
| JACK                  | 1   |                   |         | Headphone jack                    |                                                                                                                                   | Salvaged (DMG)                                                                                                                                                                               |
| R1, R2                | 2   | 1k                | 0603    | Resistor                          |                                                                                                                                   | [https://www.mouser.com/ProductDetail/YAGEO/RC0603FR-071KL?qs=VU8sRB4EgwApHsk4rF%2F3zg%3D%3D](https://www.mouser.com/ProductDetail/YAGEO/RC0603FR-071KL?qs=VU8sRB4EgwApHsk4rF%2F3zg%3D%3D)   |

## Revision History

### v2.1 (for sale)

- Add surface mount pads for tantalum capacitors, size 1411 (3528 metric)

### v2.0

- Changed holes to slots where applicable
- Made board/part measurements more accurate
- Added pads for SMT inductors for L1-L3

### v1.2

- Tented a single via

### v1.1

- Release version

## Resources
-	<a href="https://gbdev.gg8.se/files/schematics/">Rolf, bit9, and nitro2k01’s DMG schematics and layouts</a>

## License
<br />This work is licensed under a <a rel="license" href="http://creativecommons.org/licenses/by-sa/4.0/">Creative Commons Attribution-ShareAlike 4.0 International License</a>. You are able to copy and redistribute the material in any medium or format, as well as remix, transform, or build upon the material for any purpose (even commercial) - but you **must** give appropriate credit, provide a link to the license, and indicate if any changes were made.

©MouseBiteLabs 2022

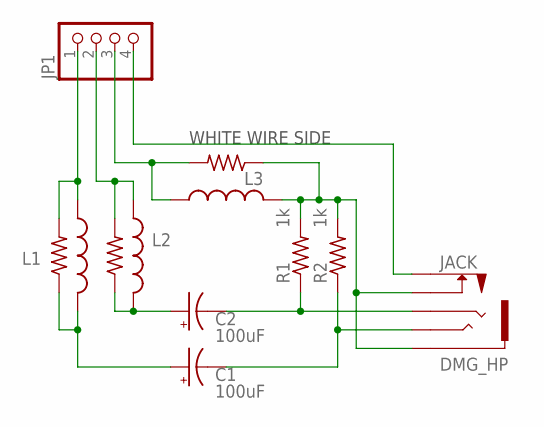
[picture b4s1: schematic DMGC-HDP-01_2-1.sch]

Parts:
C1, C2: 100uF; E2,5-5
EM1, EM2, EM9: BLM21P221SG; R0603
JACK: DMG_HP
JP1: PINHD-1X4; 1X04
L1, L2, L3: 33µH; 0204/7
R1, R2: 1k; R0603

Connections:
unnamed: EM9.2, JP1.1, L1.1
unnamed: EM2.2, JP1.3, L3.1
unnamed: EM1.2, JP1.2, L2.1
unnamed: C1.+, EM9.1, L1.2
unnamed: C2.+, EM1.1, L2.2
unnamed: EM2.1, JACK.GND (S), JACK.SWGND (SWB), L3.2, R1.2, R2.2
unnamed: JACK.SW (SWA), JP1.4
unnamed: C2.-, JACK.R, R1.1
unnamed: C1.-, JACK.T, R2.1

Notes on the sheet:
WHITE WIRE SIDE

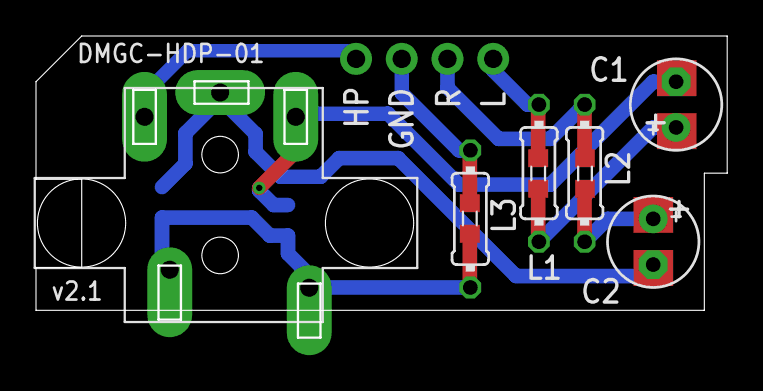
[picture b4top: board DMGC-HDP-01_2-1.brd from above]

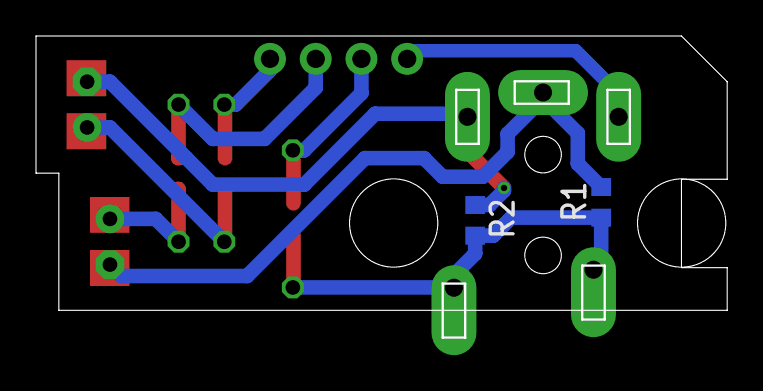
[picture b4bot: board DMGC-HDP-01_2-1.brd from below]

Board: 2 copper layers, 38.4 x 16.8 mm, 12 parts (2 on the bottom side), 9 nets.

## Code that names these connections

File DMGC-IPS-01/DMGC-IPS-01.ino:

#include <Adafruit_NeoPixel.h>
#include <EEPROM.h>

// Which pin on the Arduino is connected to the NeoPixels?
#define OUT           PCINT4 // PB4
#define pushbtn       PCINT3 // PB3
#define leftbtn       PCINT2 // PB2
#define rightbtn      PCINT1 // PB1
#define selbtn        PCINT0 // PB0

// Define order of LEDs in string, starting with 0
#define l             1
#define u             0
#define d             2
#define r             3
#define se            4
#define st            5
#define b             6
#define a             7

#define NUMPIXELS 8 // Popular NeoPixel ring size

Adafruit_NeoPixel pixels(NUMPIXELS, OUT, NEO_GRB + NEO_KHZ800);

volatile uint8_t brightness;
volatile uint8_t color_type;
const uint8_t    COLOR_QTY  = 9;
const uint8_t    DEBOUNCE_DELAY = 50;
const uint8_t    BRIGHTNESS_INC = 5;
const uint8_t    MIN_BRIGHTNESS = 5;
const uint8_t    MAX_BRIGHTNESS = 55;

volatile uint8_t brightness_change_flag = 0;

// cycles through different colors:    red  org  ylw  grn  cyan blue purp wht  off
volatile uint8_t red[COLOR_QTY]   =  { 255, 255, 255, 0,   0,   0,   255, 255, 0};
volatile uint8_t green[COLOR_QTY] =  { 0,   100, 200, 255, 255, 0,   0,   255, 0};
volatile uint8_t blue[COLOR_QTY]  =  { 0,   0,   0,   0,   255, 255, 255, 255, 0};

void setup() {

  pixels.begin();

  EEPROM.get(0, brightness);
  EEPROM.get(1, color_type);

  // Check if EPROM data was corrupted, set brightness to max or min values
  if (brightness>MAX_BRIGHTNESS){
    brightness=MAX_BRIGHTNESS;
  }
  if (brightness<MIN_BRIGHTNESS){
    brightness=MIN_BRIGHTNESS;
  }
  
  pixels.setBrightness(brightness);

  // Inputs *MUST NOT* use ATTINY's pull-ups. These will rely on the GBC CPU's internal pull-ups to 3.3V. The ATTINY is powered by 5V!!
  pinMode(pushbtn, INPUT);
  pinMode(leftbtn, INPUT);
  pinMode(rightbtn, INPUT);
  pinMode(selbtn, INPUT);

  // Skip intro if nav switch is pushed in
  if (digitalRead(pushbtn)==HIGH){

      pixels.clear();
      pixels.show();
      delay(1100);

      int y=6;
      int k=0;

      uint8_t introarray[24] = {8,8,8,8,8,8,8,2,2,0,0,6,6,3,3,5,5,5,5,5,5,5,5,5};

      // Loop through values in introarray. Delays were timed experimentally.
      for(int j=0; j<16; j++){
        for(int i=0; i<NUMPIXELS; i++){
          if(i==l){
            k=introarray[j+6];
          }
          if(i==u){
            k=introarray[j+5];
          }
          if(i==d){
            k=introarray[j+5];
          }
          if(i==r){
            k=introarray[j+4];
          }
          if(i==se){
            k=introarray[j+3];
          }
          if(i==st){
            k=introarray[j+2];
          }
          if(i==b){
            k=introarray[j+1];
          }
          if(i==a){
            k=introarray[j];
          }
        pixels.setPixelColor(i, pixels.Color(red[k],green[k],blue[k]));
        pixels.show();
        delay(y);
        }
      }
      delay(2000);
  }
}

void loop() {
  // Update LED outputs
  outputLED(color_type);

  // If nav switch is pressed
  if(digitalRead(pushbtn)==LOW){
    // Pause the program to debounce the switch, check to make sure it's still pressed
    delay(DEBOUNCE_DELAY);
    if(digitalRead(pushbtn)==LOW){

      // I'm sorry, I forgot to comment this, and now I'm reading it months later
      while(!digitalRead(pushbtn) && !digitalRead(pushbtn)){
        if(digitalRead(rightbtn)==LOW){
        delay(DEBOUNCE_DELAY);
          if(digitalRead(rightbtn)==LOW){
            while(!digitalRead(rightbtn)){
              delay(DEBOUNCE_DELAY);
            }
            if(brightness+BRIGHTNESS_INC>MAX_BRIGHTNESS){
              brightness=MAX_BRIGHTNESS;
            }else{
              brightness=brightness+BRIGHTNESS_INC;
            }
            brightness_change_flag = 1;
            pixels.setBrightness(brightness);
            outputLED(color_type);
          }
        }
        
        if(digitalRead(leftbtn)==LOW){
          delay(DEBOUNCE_DELAY);
          if(digitalRead(leftbtn)==LOW){
            while(!digitalRead(leftbtn) && !digitalRead(pushbtn)){
              delay(DEBOUNCE_DELAY);
            }
            if(brightness-BRIGHTNESS_INC<MIN_BRIGHTNESS){
              brightness=MIN_BRIGHTNESS;
            }else{
              brightness=brightness-BRIGHTNESS_INC;
            }
            brightness_change_flag = 1;
            pixels.setBrightness(brightness);
            outputLED(color_type);
          }
        }
        delay(DEBOUNCE_DELAY);
      }
      
      if(brightness_change_flag==0){
        if(color_type==COLOR_QTY-1){
          color_type=0;
        }else{
          color_type = color_type+1;
        }
      }
      // Save brightness and color setting to EPROM
      EEPROM.put(0,brightness);
      EEPROM.put(1,color_type);
      brightness_change_flag = 0;
      }
    }
  }

void outputLED(uint8_t x){
  for(int i=0; i<NUMPIXELS; i++) { // For each pixel...
    pixels.setPixelColor(i, pixels.Color(red[x],green[x],blue[x]));
    pixels.show();   // Send the updated pixel colors to the hardware.
  }  
}

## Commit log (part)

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2022-07-22 Update schematic
2022-07-22 Add files via upload
    Update schematic
2022-07-22 Add files via upload
    Update schematic, upload source files and gerbers
2022-07-22 Add files via upload
    Update master BOM
2022-07-23 Add board scans
2022-07-23 Add board blank picture
2022-07-23 Add schematic
2022-07-23 Update BOM
2022-07-23 Upload source files and gerbers
2022-07-23 Upload HEX file for LED code
2022-08-12 Update README.md
    Add assembly pictures
2022-08-12 Update README.md
    Update assembly pictures
2022-08-12 Add files via upload
    Upload gerbers, schematic, and board files
2022-08-12 Update README.md
    Update board characteristics
2022-08-12 Update README.md
    Update circuit explanation
2022-08-12 Add files via upload
    Upload updated schematic
2022-08-12 Update README.md
    Add detail on Q5 board pads
2022-08-13 Update README.md
    Updated schematic in-text
2022-08-13 Update board characteristics section
2022-08-13 Update acknowledgements section
2022-08-15 Updated BOM
2022-08-16 Update README.md
    Add photo of power switch cut
2022-08-17 Upload board scans and new schematic
2022-08-17 Upload gerbers and source files
2022-08-17 Upload schematic, board scans, and assembled pictures
2022-08-18 Add new images
2022-08-18 Add source files and gerbers
2022-08-19 Update BOM Excel
2022-08-19 Updated disclaimer
2022-08-20 Update license explanation
2022-08-26 Add version 2.0 announcement
2022-08-26 Add note about board preview tool
2022-08-29 Add screen centering note
2022-09-08 Add note about PWR board testing in assembly section
2022-09-09 Removed an errant apostrophe from "it's"
2022-09-09 Add note about taping off button pads
2022-09-15 Updated acknowledgments section
2022-09-15 Updated link to Mouser cart
2022-09-15 Add note about how to adjust the brightness of the power LED
2022-09-15 Update note about TPS63070 availability
2022-09-15 Add note about shorting EM filters
2022-09-15 Add note about EM10
2022-09-29 Update README.md
    Add note about Arduino IDE version
2022-10-01 Update README.md
    Update R1 value
2022-10-01 Update R1 value in BOM
2022-10-01 Updated discord link
2022-10-11 Added v2.0 details
2022-10-11 Add to-do list
2022-10-11 Added v2.0 information
2022-10-11 Updated to-do list
2022-10-16 Add pictures of black boards
2022-10-16 Updated with v2.0 information
2022-10-16 Add various v2.0 information
2022-10-16 Update BOM with in-stock parts
2022-10-16 Update Mouser shopping cart link
2022-10-19 Add note about programming ATTINY on-board
2022-10-19 Add programming warning
    Ensure CPU and Q5 kit ribbon cables are disconnected before programming
2022-10-20 Update in-text BOM
2022-10-23 Update with v2.0 files/info
2022-10-23 Added EM10 alternative part
2022-10-23 Add v2.0 files
2022-10-23 Add v2.0 information
2022-10-23 Update license
2022-10-23 Add HASL note
2022-10-23 Add information about silkscreen error
2022-10-23 Update v2.0 information
2022-10-23 Add note about CPU REV E
2022-10-24 Added PCBWay link
2022-10-24 Added links to PCBWay and Etsy for PCBs
2022-10-24 Add Etsy links
2022-10-25 Add pro-sound recordings
2022-10-25 Add pro-sound audio recording
2022-10-25 Add pro-sound information
2022-10-25 Update pro-sound information
2022-10-25 Update features list
2022-10-25 Update pro-sound note
2022-10-25 Update filter note
2022-10-25 Added FAQ
2022-10-25 Updated FAQ
2022-10-25 Update FAQ
2022-10-29 Add note about C3 pad size
2022-10-31 Add note about OSD buttons
2022-10-31 Update note about OSD buttons
2022-10-31 Changed 47uF part number
2022-10-31 Update Mouser cart
2022-11-11 Update Assembly section
2022-11-20 Updated revision history
2022-11-29 Add quick reference for customization
2022-12-04 Added v2.1 info
2022-12-04 Add v2.1 note
2022-12-04 Fixed README
2022-12-04 Add v2.1 files
2022-12-04 Fixed typo
2022-12-04 Add note about tantalum electrolytic capacitors
2022-12-08 Add v2.2 files
2022-12-08 Added v2.2 schematics
2022-12-09 Update revision history
2022-12-09 Add v2.2 board scans
2022-12-16 Add notes to step 1 and 2
2022-12-28 Update link to Mouser cart
2022-12-28 Update README.md
    Update BOM
2022-12-28 Fix grammar
2023-01-12 Add MachoNacho video links
2023-01-12 Updated MachoNacho link
2023-01-13 Update BOM and v2.3 information
2023-01-13 Spelling error
2023-01-13 Added v2.3 information, update BOM
2023-01-13 Add note about Neopixel disable
2023-01-13 Fix typo
2023-01-14 Add v2.3 files
2023-01-14 Add v2.3 board scan
2023-01-14 Update reset button explanation
2023-01-14 Update reset function instructions
2023-01-14 Update reset button instructions
2023-01-14 Add v2.3 board scans
2023-01-16 Add instructions for start/select tactiles
2023-01-16 Update tactile switch instructions
2023-01-16 Add reset button instructions
2023-01-16 Note about kapton tape
2023-01-16 Update assembly notes
2023-01-19 Added extra PWR board test
2023-02-08 Added referral links and discount codes
2023-03-03 Attiny sketch improvements
2023-03-12 Fix typos
2023-04-04 Moved technical explanations to Technical folder
2023-04-04 Move technical explanation to Technical folder
2023-04-09 Add note about Arduino programming
2023-04-15 Update holes per Cody
2024-08-21 Update EM6-EM8 part number
